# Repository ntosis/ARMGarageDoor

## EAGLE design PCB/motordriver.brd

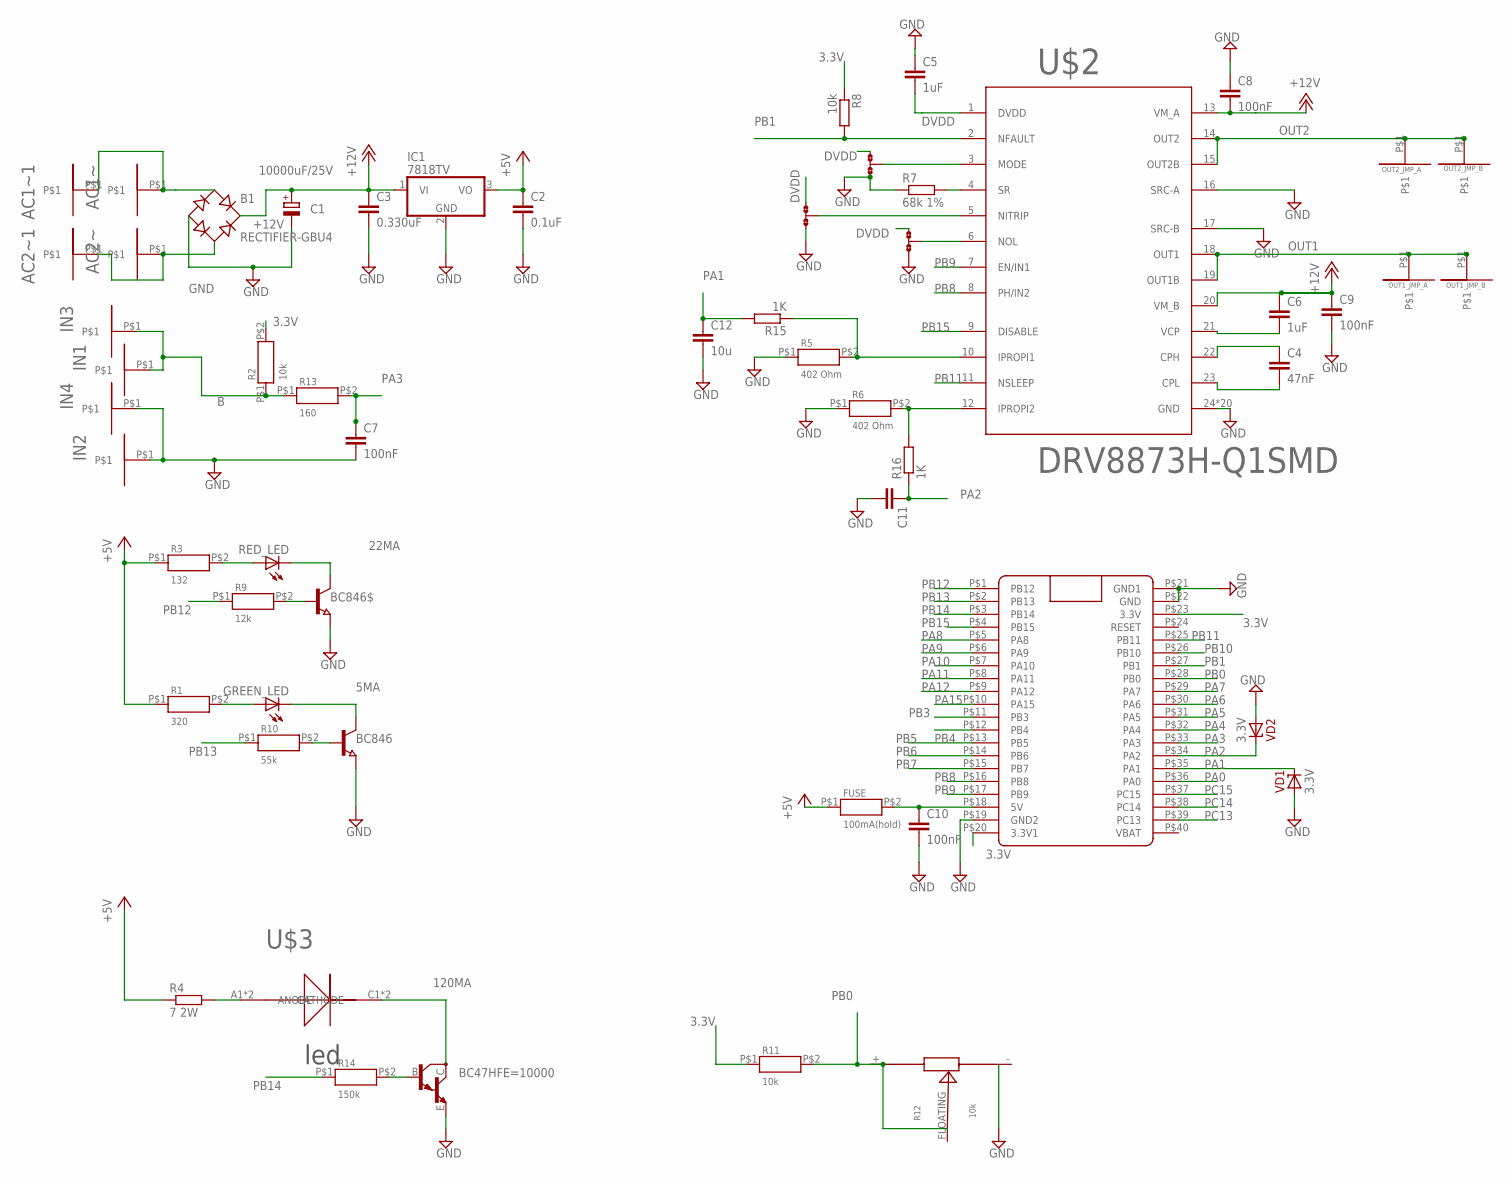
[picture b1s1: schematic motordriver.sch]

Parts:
AC1~, AC1~1, AC2~, AC2~1: SMDPAD; 1.5X7MMPAD
B1: RECTIFIER-GBU4; GBU4
BC47HFE=10000: MMBTA14LT1; SOT23-BEC
BC846, BC846$: NPN-TRANSISTOR_SOT23; SOT23
C1: 10000uF/25V; E7,5-18
C2: 0.1uF; C1206
C3: 0.330uF; C1206
C4: 47nF; C1206K
C5, C6: 1uF; C1206K
C7: 100nF; C1206
C8, C9: 100nF; C0805
C10: 100nF; C0805K
C11: C-EUC0805K; C0805K
C12: 10u; C0805K
FUSE: 100mA(hold); 0805
GREEN_LED: LEDCHIPLED_0805; CHIPLED_0805
IC1: 7818TV; TO220V
IN1, IN2, IN3, IN4: SMDPAD; 1.5X7MMPAD
JMP1, JMP2, JMP3: 0R-JUMPA; A0R-JMP
OUT1_JMP_A, OUT1_JMP_B, OUT2_JMP_A, OUT2_JMP_B: SMDPAD; 1.5X7MMPAD
R1: 320; 0805
R2, R11: 10k; 0805
R3: 132; 0805
R4: 7 2W; R1210
R5, R6: 402 Ohm; 0805
R7: 68k 1%; R0805
R8: 10k; R0805
R9: 12k; 0805
R10: 55k; 0805
R12: 10k; 3X1MM
R13: 160; 0805
R14: 150k; 0805
R15, R16: 1K; R0805
RED_LED: LEDCHIPLED_0805; CHIPLED_0805
U$1: BLUE_PILL
U$2: DRV8873H-Q1SMD; HTSSOP24
U$3: POWER_LED; OSRAMLED
VD1, VD2: 3.3V; DO35-7

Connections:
3.3V: R2.P$2, R8.1, R11.P$1, U$1.P$20 (3.3V1), U$1.P$23 (3.3V)
5MA: BC846.3 (C), GREEN_LED.C
22MA: BC846$.3 (C), RED_LED.C
120MA: BC47HFE=10000.C, U$3.C1 (CATHODE), U$3.C2 (CATHODE)
+5V: C2.1, FUSE.P$1, IC1.3 (VO), R1.P$1, R3.P$1, R4.1
+12V: B1.+, C1.+, C3.1, C6.1, C8.2, C9.1, IC1.1 (VI), U$2.13 (VM_A), U$2.20 (VM_B)
B: IN1.P$1, IN3.P$1, R2.P$1, R13.P$1
DVDD: C5.2, JMP1.1, JMP2.1, JMP3.1, U$2.1 (DVDD)
GND: B1.-, BC47HFE=10000.E, BC846.2 (E), BC846$.2 (E), C1.-, C2.2, C3.2, C5.1, C7.2, C8.1, C9.2, C10.2, C11.2, C12.2, IC1.2 (GND), IN2.P$1, IN4.P$1, JMP1.3, JMP2.3, JMP3.3, R5.P$1, R6.P$1, R7.1, R12.-, U$1.P$19 (GND2), U$1.P$21 (GND1), U$1.P$22 (GND), U$2.16 (SRC-A), U$2.17 (SRC-B), U$2.24 (GND), U$2.GND_ (GND), U$2.P$1 (GND), U$2.P$2 (GND), U$2.P$3 (GND), U$2.P$4 (GND), U$2.P$5 (GND), U$2.P$6 (GND), U$2.P$7 (GND), U$2.P$8 (GND), U$2.P$9 (GND), U$2.P$10 (GND), U$2.P$11 (GND), U$2.P$12 (GND), U$2.P$13 (GND), U$2.P$14 (GND), U$2.P$15 (GND), U$2.P$16 (GND), U$2.P$18 (GND), U$2.P$19 (GND), VD1.A, VD2.A
unnamed: AC1~.P$1, AC1~1.P$1, B1.AC1
unnamed: AC2~.P$1, AC2~1.P$1, B1.AC2
unnamed: C4.1, U$2.22 (CPH)
unnamed: C4.2, U$2.23 (CPL)
unnamed: JMP2.2, U$2.6 (NOL)
unnamed: JMP1.2, U$2.5 (NITRIP)
unnamed: JMP3.2, U$2.3 (MODE)
unnamed: R7.2, U$2.4 (SR)
unnamed: C6.2, U$2.21 (VCP)
unnamed: R3.P$2, RED_LED.A
unnamed: GREEN_LED.A, R1.P$2
unnamed: BC846$.1 (B), R9.P$2
unnamed: BC846.1 (B), R10.P$2
unnamed: R4.2, U$3.A1 (ANODE), U$3.A2 (ANODE)
unnamed: BC47HFE=10000.B, R14.P$2
unnamed: C10.1, FUSE.P$2, U$1.P$18 (5V)
unnamed: R5.P$2, R15.1, U$2.10 (IPROPI1)
unnamed: R6.P$2, R16.2, U$2.12 (IPROPI2)
OUT1: OUT1_JMP_A.P$1, OUT1_JMP_B.P$1, U$2.18 (OUT1), U$2.19 (OUT1B)
OUT2: OUT2_JMP_A.P$1, OUT2_JMP_B.P$1, U$2.14 (OUT2), U$2.15 (OUT2B)
PA0: U$1.P$36 (PA0)
PA1: C12.1, R15.2, U$1.P$35 (PA1), VD1.C
PA2: C11.1, R16.1, U$1.P$34 (PA2), VD2.C
PA3: C7.1, R13.P$2, U$1.P$33 (PA3)
PA4: U$1.P$32 (PA4)
PA5: U$1.P$31 (PA5)
PA6: U$1.P$30 (PA6)
PA7: U$1.P$29 (PA7)
PA8: U$1.P$5 (PA8)
PA9: U$1.P$6 (PA9)
PA10: U$1.P$7 (PA10)
PA11: U$1.P$8 (PA11)
PA12: U$1.P$9 (PA12)
PA15: U$1.P$10 (PA15)
PB0: R11.P$2, R12.+, R12.FLOATING, U$1.P$28 (PB0)
PB1: R8.2, U$1.P$27 (PB1), U$2.2 (NFAULT)
PB3: U$1.P$11 (PB3)
PB4: U$1.P$12 (PB4)
PB5: U$1.P$13 (PB5)
PB6: U$1.P$14 (PB6)
PB7: U$1.P$15 (PB7)
PB8: U$1.P$16 (PB8), U$2.8 (PH/IN2)
PB9: U$1.P$17 (PB9), U$2.7 (EN/IN1)
PB10: U$1.P$26 (PB10)
PB11: U$1.P$25 (PB11), U$2.11 (NSLEEP)
PB12: R9.P$1, U$1.P$1 (PB12)
PB13: R10.P$1, U$1.P$2 (PB13)
PB14: R14.P$1, U$1.P$3 (PB14)
PB15: U$1.P$4 (PB15), U$2.9 (DISABLE)
PC13: U$1.P$39 (PC13)
PC14: U$1.P$38 (PC14)
PC15: U$1.P$37 (PC15)

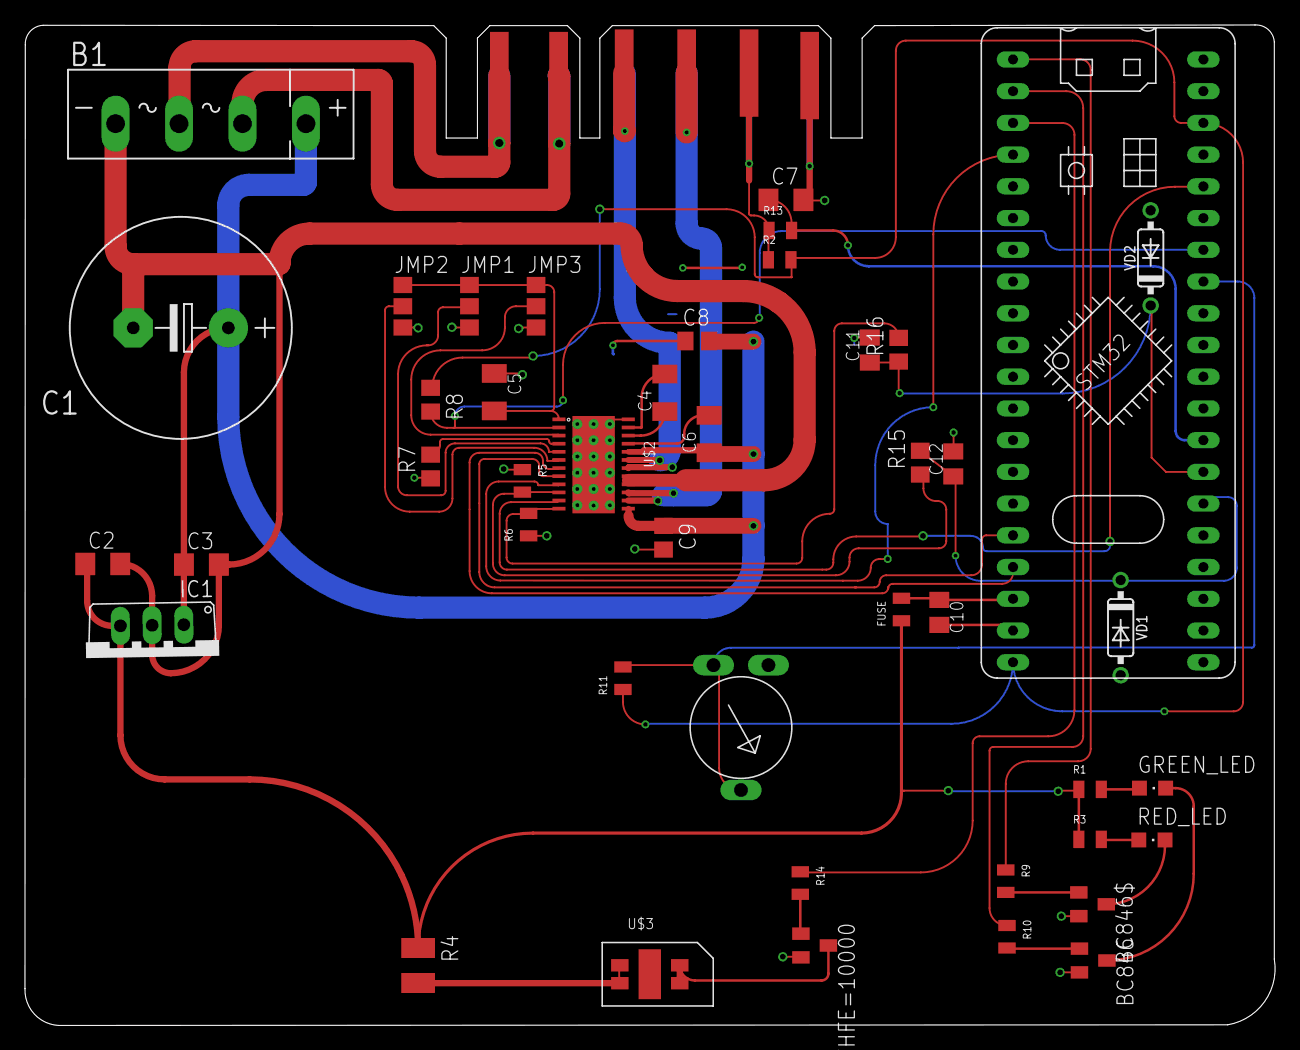
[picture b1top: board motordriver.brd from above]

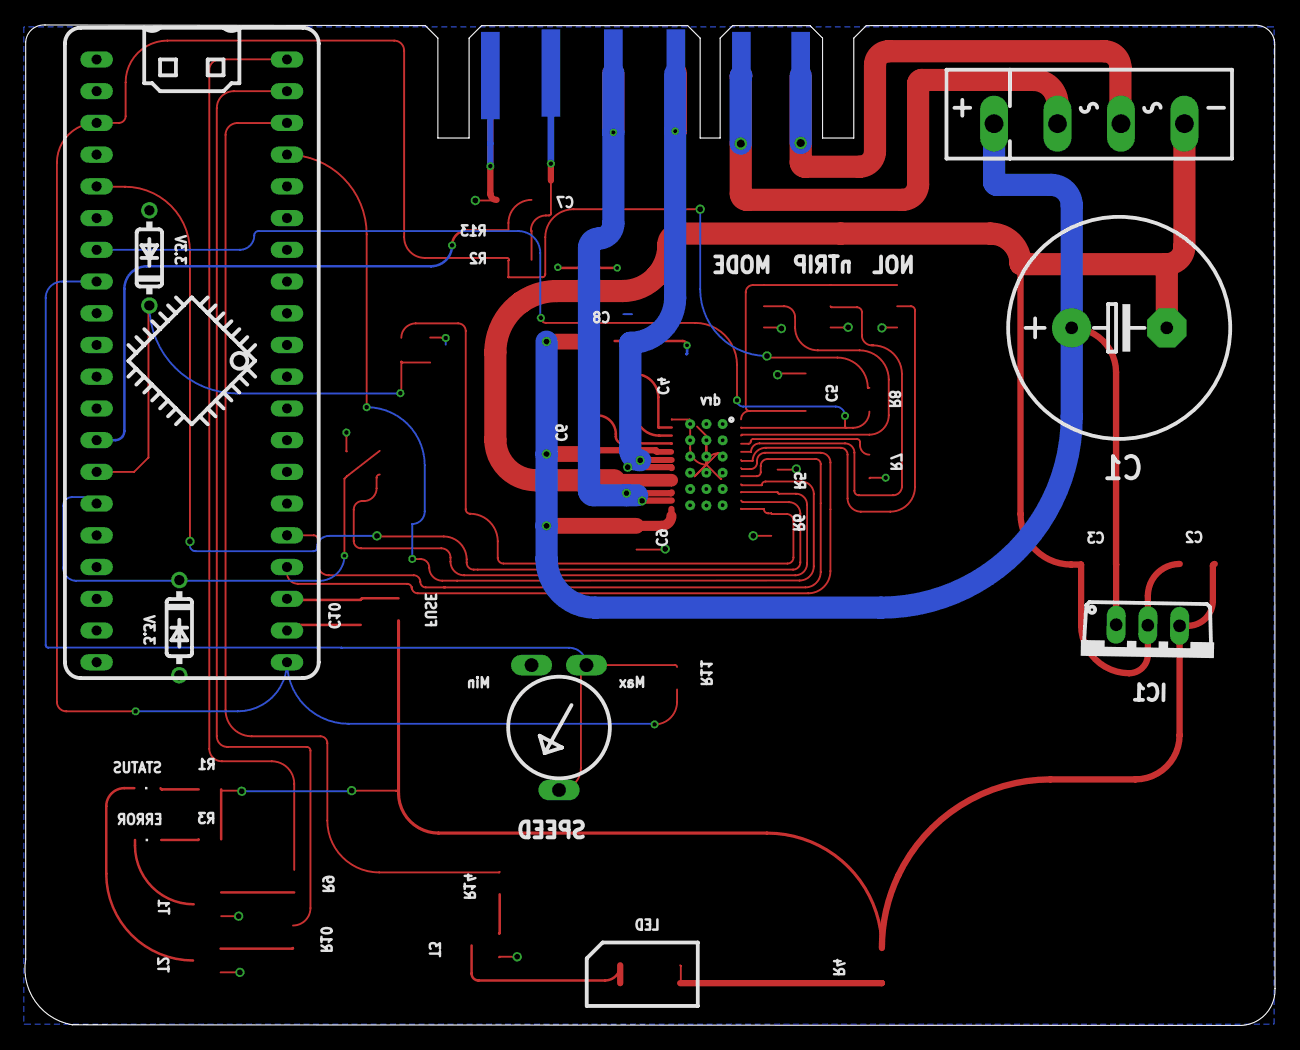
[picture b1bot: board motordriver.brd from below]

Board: 2 copper layers, 100.1 x 80.1 mm, 56 parts (6 on the bottom side), 41 nets.

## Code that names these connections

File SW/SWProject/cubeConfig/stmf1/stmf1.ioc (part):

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Mcu.Name=STM32F103C(8-B)Tx
Mcu.Package=LQFP48
Mcu.UserName=STM32F103C8Tx
PA1.GPIOParameters=GPIO_Mode
PA1.GPIO_Mode=GPIO_MODE_ANALOG
PA1.Signal=ADCx_IN1
PA13.Mode=Serial_Wire
PA13.Signal=SYS_JTMS-SWDIO
PA14.Mode=Serial_Wire
PA14.Signal=SYS_JTCK-SWCLK
PA2.GPIOParameters=GPIO_Mode
PA2.GPIO_Mode=GPIO_MODE_ANALOG
PA2.Signal=ADCx_IN2
PA3.GPIOParameters=GPIO_PuPd,GPIO_Mode
PA3.GPIO_Mode=GPIO_MODE_INPUT
PA3.GPIO_PuPd=GPIO_NOPULL
PA3.Signal=GPIO_Input
PB0.GPIOParameters=GPIO_Mode
PB0.GPIO_Mode=GPIO_MODE_ANALOG
PB0.Signal=ADCx_IN8
PB1.GPIOParameters=GPIO_PuPd,GPIO_Mode
PB1.GPIO_Mode=GPIO_MODE_INPUT
PB1.GPIO_PuPd=GPIO_NOPULL
PB1.Signal=GPIO_Input
PB11.GPIOParameters=GPIO_Speed,PinState,GPIO_PuPd,GPIO_ModeDefaultOutputPP
PB11.GPIO_ModeDefaultOutputPP=GPIO_MODE_OUTPUT_PP
PB11.GPIO_PuPd=GPIO_NOPULL
PB11.GPIO_Speed=GPIO_SPEED_FREQ_LOW
PB11.PinState=GPIO_PIN_RESET
PB11.Signal=GPIO_Output
PB12.GPIOParameters=GPIO_Speed,PinState,GPIO_PuPd,GPIO_ModeDefaultOutputPP
PB12.GPIO_ModeDefaultOutputPP=GPIO_MODE_OUTPUT_PP
PB12.GPIO_PuPd=GPIO_NOPULL
PB12.GPIO_Speed=GPIO_SPEED_FREQ_LOW
PB12.PinState=GPIO_PIN_RESET
PB12.Signal=GPIO_Output
PB13.GPIOParameters=GPIO_Speed,PinState,GPIO_PuPd,GPIO_ModeDefaultOutputPP
PB13.GPIO_ModeDefaultOutputPP=GPIO_MODE_OUTPUT_PP
PB13.GPIO_PuPd=GPIO_NOPULL
PB13.GPIO_Speed=GPIO_SPEED_FREQ_LOW
PB13.PinState=GPIO_PIN_RESET
PB13.Signal=GPIO_Output
PB14.GPIOParameters=GPIO_Speed,PinState,GPIO_PuPd,GPIO_ModeDefaultOutputPP
PB14.GPIO_ModeDefaultOutputPP=GPIO_MODE_OUTPUT_PP
PB14.GPIO_PuPd=GPIO_NOPULL
PB14.GPIO_Speed=GPIO_SPEED_FREQ_LOW
PB14.PinState=GPIO_PIN_RESET
PB14.Signal=GPIO_Output
PB15.GPIOParameters=GPIO_Speed,PinState,GPIO_PuPd,GPIO_ModeDefaultOutputPP
PB15.GPIO_ModeDefaultOutputPP=GPIO_MODE_OUTPUT_PP
PB15.GPIO_PuPd=GPIO_NOPULL
PB15.GPIO_Speed=GPIO_SPEED_FREQ_LOW
PB15.PinState=GPIO_PIN_RESET
PB15.Signal=GPIO_Output
PB8.Signal=S_TIM4_CH3
PB9.Signal=S_TIM4_CH4
PC14-OSC32_IN.Mode=LSE-External-Oscillator
PC14-OSC32_IN.Signal=RCC_OSC32_IN
PC15-OSC32_OUT.Mode=LSE-External-Oscillator
PC15-OSC32_OUT.Signal=RCC_OSC32_OUT
PD0-OSC_IN.Mode=HSE-External-Oscillator
PD0-OSC_IN.Signal=RCC_OSC_IN
PD1-OSC_OUT.Mode=HSE-External-Oscillator
PD1-OSC_OUT.Signal=RCC_OSC_OUT
RCC.SYSCLKFreq_VALUE=72000000
RCC.SYSCLKSource=RCC_SYSCLKSOURCE_PLLCLK
board=custom

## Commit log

2019-05-10 Initial creation of the Project
2019-05-10 Init of matlab model.
2019-05-10 create the first input and output signals
2019-05-11 develop the model. Added data dictionary
2019-05-11 Simulation is working. Motor derection and on/off seems ok.
2019-05-11 set Zero current error during the motor is active.
2019-05-11 add saturation on overflow for the light.
2019-05-13 added parameters in data dictionary.
2019-05-17 Added the PCB init files.
2019-05-20 work in PCB
2019-05-22 work in board
2019-05-22 more work in board
2019-05-31 PCB/motordriver.sch
2019-06-01 troubles with data dictionary
2019-06-01 added datadictionary
2019-06-07 basic software delepment before final release.
2019-06-07 some changes in resistor values.
2019-06-12 fixed the error handlig to stop the motor permanent.
2019-06-12 fixed forgotten signal must resolved.
2019-06-12 software is working. Send the sum of Iprop1 and Iprop2 to application software.
2019-06-13 This revision is working.
2019-06-13 set unit delay init state to zero, to avoid light on after reset.
2019-07-03 added Low pass rc filter for the IOPROPx output
2019-07-21 * Change tunable parameter to name "DebounceStepsToSetminmaxCurrError_C"
    * Add the Simulink Software as library.
2019-07-21 * Added the Simulink library.
2019-08-19 Added Matlab headers and fix the maximum value for the poti in the map function.
2019-08-19 use the applicationSW.lib to link the software.
2019-10-20 EEprom emulation is working for write and read block. Should be updated for transfer page.
2019-10-23 EEprom Emulation is working but this is a draft commit to save the changes.
2019-10-27 CRC Check is working in eeprom emulation. Data write and read is checked.
2019-10-29 Added monitor unit for errors and a new global function to save the struct in eeprom.
2019-10-29 added the files for monitor unit.
2019-12-10 Revert "added the files for monitor unit."
    This reverts commit 0df1ae1de50778cfaab4986af6c86d66bd3b244c.
2019-12-19 working on variant software. Draft commit.
